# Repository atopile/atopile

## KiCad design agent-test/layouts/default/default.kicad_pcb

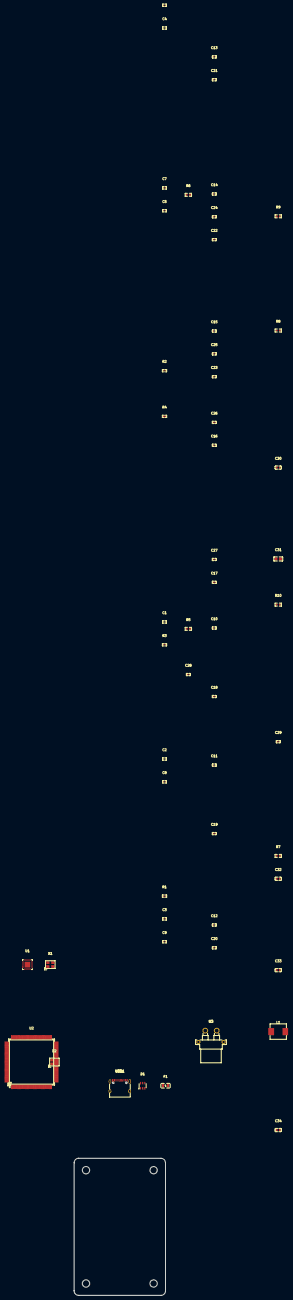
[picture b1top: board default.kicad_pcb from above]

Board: 2 copper layers, 40.0 x 60.0 mm, 54 parts (0 on the bottom side), 25 nets, no tracks yet.

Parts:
BS1: RectangularBoardShape
C1, C2, C3, C4, C5, C6, C7, C8, C9, C10, C11, C12, C13, C14, C15, C16, C17, C18, C19, C20, C21, C22, C23, C24, C25, C26, C27, C28, C29: 0F; C0402
C30, C32, C33, C34: 0F; C0603
C31: 0F; C0805
D1: SOT-23-6_L2.9-W1.6-P0.95-LS2.8-BL
F1: F0805
L1: L 0H; IND-SMD_L7.3-W6.6_MHCI06030
R1, R3: 100000Ω; R0402
R2: 12100Ω; R0402
R4: 10000Ω; R0402
R5, R6, R9: 10000Ω; R0603
R7: 6490Ω; R0603
R8: 56000Ω; R0603
R10: 20000Ω; R0603
U1: QFN-24_L4.0-W4.0-P0.50-TL-EP2.5
U2: LQFP-144_L20.0-W20.0-P0.50-LS22.0-BL
U3: CONN-TH_XT30PW-F-1
USB1: USB-C-SMD_TYPE-C-6PIN-2MD-073
X1, X2: OSC-SMD_4P-L3.2-W2.5-BL_SIT8008BI

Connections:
10: R1.1, U1.10
DATA_N: D1.1, D1.6, U2.103, USB1.5, USB1.7
DATA_P: D1.3, D1.4, U2.104, USB1.6, USB1.8
ETH_LED_LINK: R3.1, U1.3
RBIAS: R2.1, U1.24
RX_P: U1.12, U2.102
TX_P: U1.13, U2.101
XIN: C22.1, U2.23, X2.1
XOUT: C23.1, U2.24, X2.3
anode: C32.1, U3.1
cathode: C1.2, C2.2, C3.2, C4.2, C5.2, C6.2, C7.2, C8.2, C9.2, C10.2, C11.2, C12.2, C13.2, C14.2, C15.2, C16.2, C17.2, C18.2, C19.2, C20.2, C21.2, C22.2, C23.2, C24.2, C25.2, C26.2, C27.2, C30.2, C31.2, C32.2, C33.2, C34.2, R1.2, R2.2, R3.2, R7.2, R9.2, U1.25, U2.16, U2.31, U2.38, U2.51, U2.61, U2.83, U2.94, U2.107, U2.120, U2.130, U3.2, X1.2, X1.4, X2.2, X2.4
cc[0]-4: R5.1, USB1.4
cc[1]-10: R6.1, USB1.10
cff-power-hv: C29.1, R8.2
cff-power-lv: C29.2, R7.1
decoupling_capacitor-power-hv: C28.1, D1.5, F1.2
hv: C6.1, C7.1, U1.6
lv: C28.2, D1.2, R5.2, R6.2, USB1.1, USB1.12, USB1.13, USB1.14, USB1.15, USB1.16
nRST: R4.1, U1.15
power_vbus-hv: F1.1, USB1.2, USB1.11
unnamed[0]: R9.1, R10.2
vcap_caps[1]-power-hv: C24.1, C25.1, U2.71, U2.106
vref_caps[1]-power-cathode: C1.1, C2.1, C3.1, C4.1, C5.1, C10.1, C11.1, C12.1, C13.1, C14.1, C15.1, C16.1, C17.1, C18.1, C19.1, C20.1, C21.1, C26.1, C27.1, C30.1, C31.1, C33.1, C34.1, L1.2, R4.2, R8.1, R10.1, U1.1, U1.9, U1.19, U2.17, U2.30, U2.32, U2.33, U2.39, U2.52, U2.62, U2.72, U2.84, U2.95, U2.108, U2.121, U2.131, U2.144
xtal_caps[0]-power-hv: C8.1, U1.5, X1.1
xtal_caps[1]-power-hv: C9.1, U1.4, X1.3

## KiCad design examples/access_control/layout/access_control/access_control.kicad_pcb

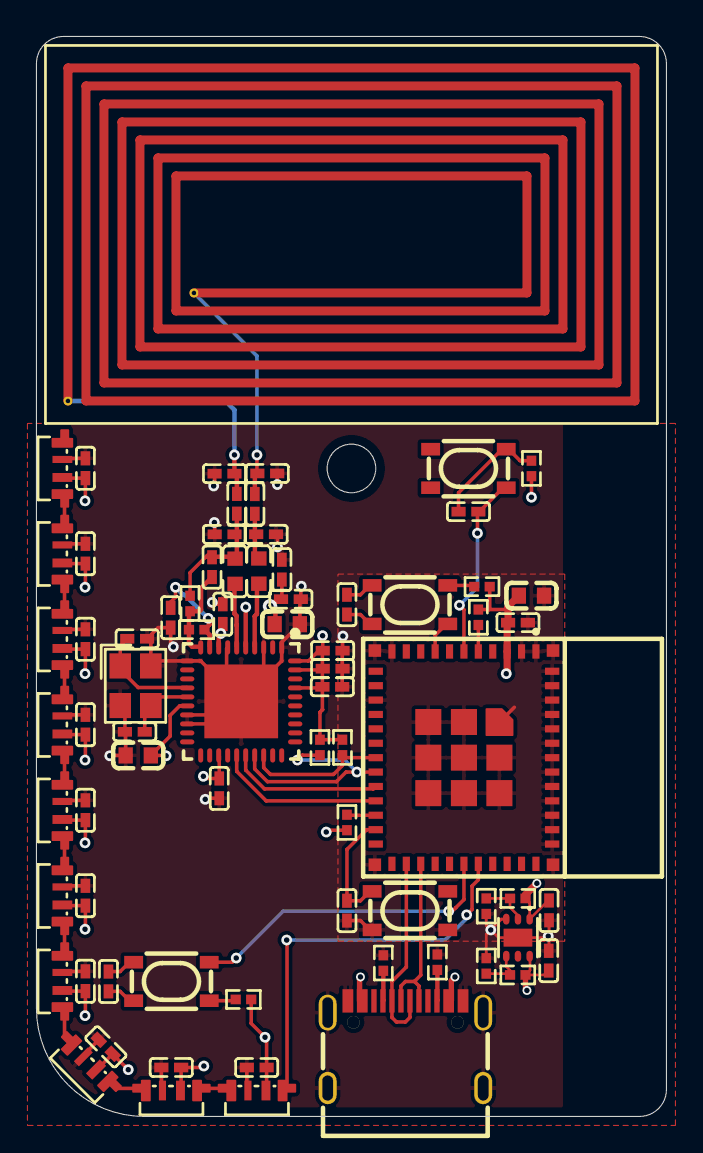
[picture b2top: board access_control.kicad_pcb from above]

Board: 4 copper layers, 35.0 x 60.0 mm, 74 parts (0 on the bottom side), 42 nets.

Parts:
ANT1: NFCAntenna
C1, C2: 1µF ±10% 25V X5R; C0402
C3, C4, C5, C6, C7, C8, C9, C10, C11, C12, C13, C14, C16, C17, C18, C22, C24, C25, C26, C27, C30, C33, C34, C35, C36, C37: 100nF ±10% 16V X7R; C0402
C15: 22µF ±20% 6.3V X5R; C0603
C19, C20: 20pF ±5% 50V C0G; C0402
C21, C23: 10µF ±20% 6.3V X5R; C0603
C28, C31: 100pF ±5% 50V C0G; C0402
C29, C32: 220pF ±10% 50V X7R; C0402
L1, L2: IND-SMD_L1.6-W0.8-1
R1, R2, R6, R7, R8, R9, R12, R13: 10kΩ ±1% 62.5mW; R0402
R3: 47kΩ ±1% 62.5mW; R0402
R4: 150kΩ ±1% 62.5mW; R0402
R5: 2kΩ ±1% 62.5mW; R0402
R10, R11: 1kΩ ±1% 62.5mW; R0402
R14, R15: 4.7kΩ ±1% 62.5mW; R0402
SW1, SW2, SW3, SW4: KEY-SMD_4P-L4.2-W3.2-P2.20-LS4.6
U1: WSON-6_L2.0-W2.0-P0.65-TL-EP
U2, U3, U4, U5, U6, U7, U8, U9, U10, U11: LED-SMD_4P-L3.5-W1.6_SK6805SIDE-G-001
U12: WIFIM-SMD_ESP32-C3-MINI-1
U13: QFN-40_L6.0-W6.0-P0.50-BL-EP4.1
USB1: USB-C-SMD_KH-TYPE-C-16P
X1: CRYSTAL-SMD_4P-L3.2-W2.5-BL

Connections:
-DOUT-0: U2.1, U3.4
-DOUT-1: U3.1, U4.4
-DOUT-2: U4.1, U5.4
-DOUT-3: U5.1, U6.4
-DOUT-4: U6.1, U7.4
-DOUT-5: U7.1, U8.4
-DOUT-6: U8.1, U9.4
-DOUT-7: U9.1, U10.4
-DOUT-8: U10.1, U11.4
-line-0: ANT1.1, C31.1, C33.2
-line-1: ANT1.2, C28.1, C30.2
A5: R14.1, USB1.A5
B5: R15.1, USB1.B5
EN: R3.1, R4.2, U1.4
FB: R5.1, R6.2, U1.2
RX: C26.2, R10.2, R11.2, U13.10
TX1: L1.2, U13.4
TX2: L2.2, U13.6
VMID: C35.1, R11.1, U13.9
gnd: C1.2, C2.2, C3.2, C4.2, C5.2, C6.2, C7.2, C8.2, C9.2, C10.2, C11.2, C12.2, C13.1, C15.2, C16.2, C17.2, C18.2, C19.2, C20.2, C21.2, C22.2, C23.2, C24.2, C25.2, C27.2, C28.2, C29.2, C31.2, C32.2, C34.2, C35.2, R3.2, R5.2, R14.2, R15.2, SW3.1, SW3.2, U1.3, U1.7, U2.2, U3.2, U4.2, U5.2, U6.2, U7.2, U8.2, U9.2, U10.2, U11.2, U12.1, U12.2, U12.11, U12.14, U12.36, U12.37, U12.38, U12.39, U12.40, U12.41, U12.42, U12.43, U12.44, U12.45, U12.46, U12.47, U12.48, U12.49, U12.50, U12.51, U12.52, U12.53, U13.1, U13.3, U13.7, U13.11, U13.17, U13.18, U13.41, USB1.1, USB1.2, USB1.3, USB1.4, USB1.A1, USB1.A12, USB1.B1, USB1.B12, X1.2, X1.4
hv-0: C1.1, C3.1, C4.1, C5.1, C6.1, C7.1, C8.1, C9.1, C10.1, C11.1, C12.1, C15.1, C16.1, C17.1, C18.1, C21.1, C22.1, C23.1, C24.1, C25.1, C27.1, C34.1, R1.2, R2.2, R6.1, R7.2, R8.2, R9.2, R12.2, R13.2, U1.1, U2.3, U3.3, U4.3, U5.3, U6.3, U7.3, U8.3, U9.3, U10.3, U11.3, U12.3, U13.5, U13.8, U13.16, U13.23, U13.37, U13.39, U13.40
hv-1: C2.1, R4.1, U1.6, USB1.A4, USB1.A9, USB1.B4, USB1.B9
input-0: C36.1, R1.1, SW1.1, SW1.2
input-1: C37.1, R2.1, SW2.1, SW2.2
input-2: C14.1, R9.1, SW4.1, SW4.2
line-2: R7.1, U12.5
line-3: R12.1, U12.18, U13.28
line-4: R13.1, U12.19, U13.27
line-6: U12.26, USB1.A7, USB1.B7
line-7: U12.27, USB1.A6, USB1.B6
line-8: U2.4, U12.31
line-9: U12.20, U13.26
line-10: U12.21, U13.25
line-11: R8.1, U12.22
nfc_reader-input: C19.1, U13.14, X1.1
nfc_reader-output: C20.1, U13.15, X1.3
output-0: C14.2, SW4.3, SW4.4, U12.8
output-1: C36.2, SW1.3, SW1.4, U12.6
output-2: C37.2, SW2.3, SW2.4, U12.30
output-3: C13.2, SW3.3, SW3.4, U12.23
tx_1_mid: C29.1, C30.1, L1.1
tx_2_mid: C26.1, C32.1, C33.1, L2.1, R10.1

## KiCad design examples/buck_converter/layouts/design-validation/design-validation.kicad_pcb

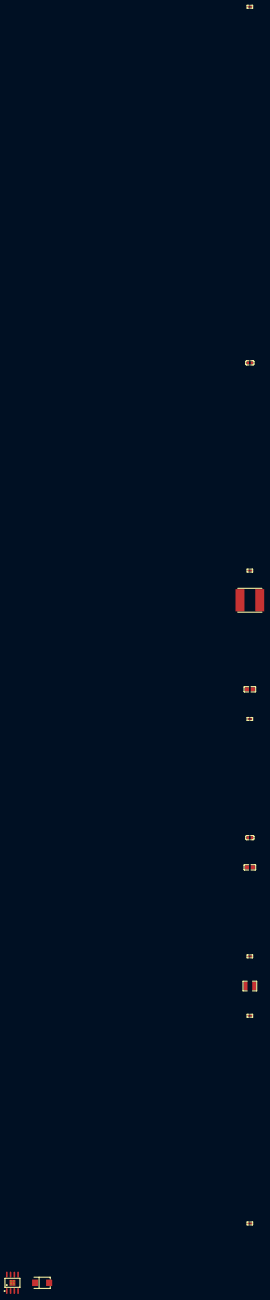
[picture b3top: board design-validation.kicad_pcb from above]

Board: 2 copper layers, 14 parts (0 on the bottom side), 10 nets, no tracks yet.

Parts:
C1, C2: 0F; C0603
C3, C4: 0F; C0805
D1: SMB_L4.6-W3.6-LS5.3-RD
L1: L 0H; IND-SMD_L8.0-W8.0
R1: 10200Ω; R0402
R2: 16900Ω; R0402
R3: 91000Ω; R0402
R4: 450000Ω; R0402
R5: 1Ω; R1210
R6: 240000Ω; R0402
R7: 53600Ω; R0402
U1: SOIC-8_L5.0-W4.0-P1.27-LS6.0-BL-EP2.0

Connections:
EN: R3.1, R4.2, U1.3
FB: R1.1, R7.2, U1.5
RT_CLK: R6.1, U1.4
anode: C2.2, C3.2, C4.2, D1.2, R1.2, R3.2, R5.2, R6.2, U1.7, U1.9
c_comp1-power-hv: C2.1, R2.1, U1.6
c_comp-power-hv: C3.1, R2.2
cathode: C1.2, D1.1, L1.1, U1.8
hv: C1.1, U1.1
power_in-hv: C4.1, R4.1, U1.2
power_out-hv: L1.2, R5.1, R7.1

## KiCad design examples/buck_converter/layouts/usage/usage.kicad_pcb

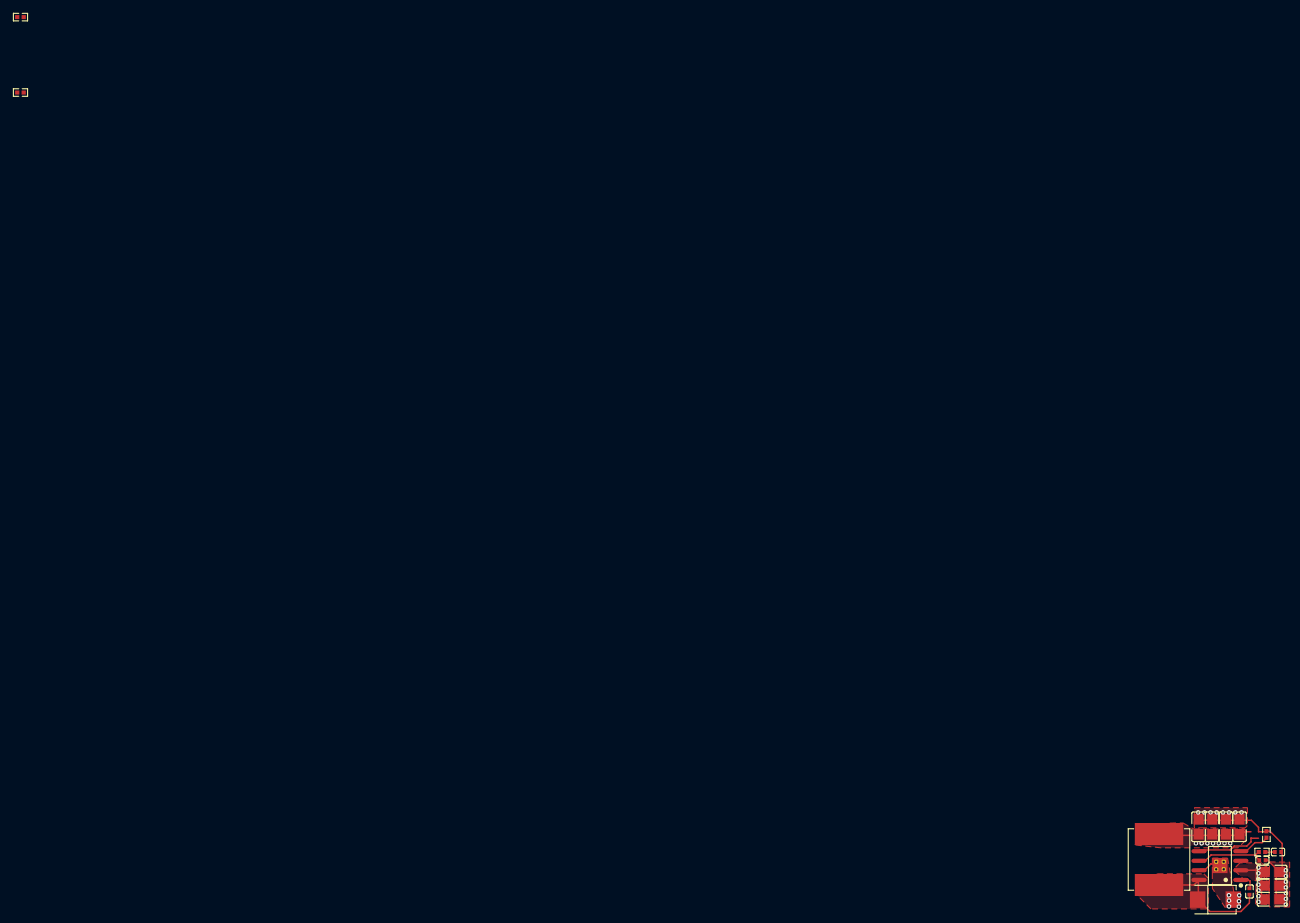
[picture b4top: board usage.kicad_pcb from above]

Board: 2 copper layers, 17 parts (0 on the bottom side), 9 nets.

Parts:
C1, C2, C3: 0F; C0402
C4, C5, C6, C7, C8, C9, C10: 0F; C0805
D1: SMB_L4.6-W3.6-LS5.3-RD
L1: L 0H; IND-SMD_L8.0-W8.0_SWPA8040S
R1: 23700Ω; R0402
R2: 51000Ω; R0402
R3: 10000Ω; R0402
R4: 162000Ω; R0402
U1: SOIC-8_L5.0-W4.0-P1.27-LS6.0-BL-EP2.0

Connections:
RT_CLK: R4.1, U1.4
anode: C2.2, C3.2, C4.2, C5.2, C6.2, C7.2, C8.2, C9.2, C10.2, D1.2, R3.2, R4.2, U1.7, U1.9
bootstrap_capacitor-power-hv: C1.1, U1.1
cathode: C1.2, D1.1, L1.1, U1.8
compensation_capacitors[0]-power-hv: C2.1, R1.2
compensation_capacitors[1]-power-hv: C3.1, R1.1, U1.6
hv: C4.1, C5.1, C6.1, U1.2, U1.3
power_out-hv: C7.1, C8.1, C9.1, C10.1, L1.2, R2.1
ref_out-hv: R2.2, R3.1, U1.5
